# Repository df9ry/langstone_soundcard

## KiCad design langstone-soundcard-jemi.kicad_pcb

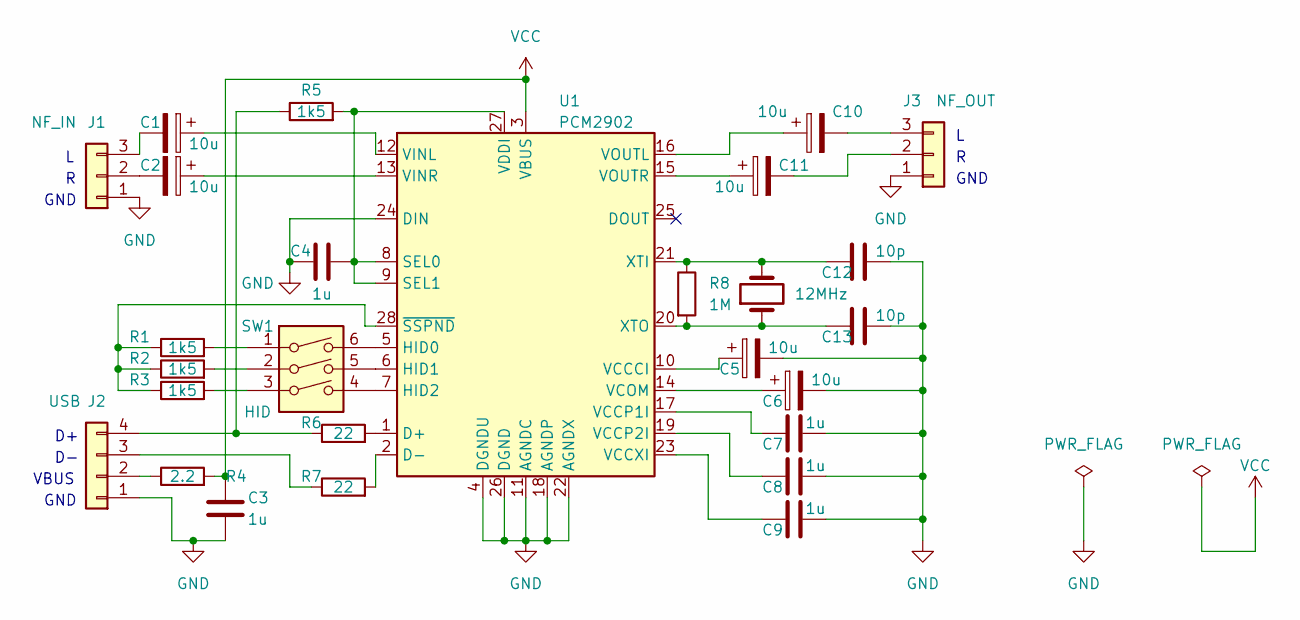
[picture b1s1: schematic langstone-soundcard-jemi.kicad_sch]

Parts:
C1, C2, C5, C6, C10, C11: 10u; CP_EIA-3216-18_Kemet-A_Pad1.58x1.35mm_HandSolder
C3, C4, C7, C8, C9: 1u; C_0603_1608Metric_Pad1.08x0.95mm_HandSolder
C12, C13: 10p; C_0603_1608Metric_Pad1.08x0.95mm_HandSolder
J1: NF_IN; JST_PH_B3B-PH-K_1x03_P2.00mm_Vertical
J2: USB; JST_PH_B4B-PH-K_1x04_P2.00mm_Vertical
J3: NF_OUT; JST_PH_B3B-PH-K_1x03_P2.00mm_Vertical
R1, R2, R3, R5: 1k5; R_0603_1608Metric_Pad0.98x0.95mm_HandSolder
R4: 2.2; R_0603_1608Metric_Pad0.98x0.95mm_HandSolder
R6, R7: 22; R_0603_1608Metric_Pad0.98x0.95mm_HandSolder
R8: 1M; R_0603_1608Metric_Pad0.98x0.95mm_HandSolder
SW1: HID; SW_DIP_SPSTx03_Slide_KingTek_DSHP03TJ_W5.25mm_P1.27mm_JPin
U1: PCM2902; SSOP-28_5.3x10.2mm_P0.65mm
Y1: 12MHz; Crystal_SMD_G8-2Pin_3.2x1.5mm_HandSoldering

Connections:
GND: C3.2, C4.1, C5.2, C6.2, C7.2, C8.2, C9.2, C12.2, C13.2, J1.1, J2.1, J3.1, U1.4 (DGNDU), U1.11 (AGNDC), U1.18 (AGNDP), U1.22 (AGNDX), U1.24 (DIN), U1.26 (DGND)
unnamed: C1.1, U1.12 (VINL)
unnamed: C1.2, J1.3
unnamed: C2.1, U1.13 (VINR)
unnamed: C2.2, J1.2
unnamed: C4.2, R5.2, U1.8 (SEL0), U1.9 (SEL1), U1.27 (VDDI)
unnamed: C5.1, U1.10 (VCCCI)
unnamed: C6.1, U1.14 (VCOM)
unnamed: C7.1, U1.17 (VCCP1I)
unnamed: C8.1, U1.19 (VCCP2I)
unnamed: C9.1, U1.23 (VCCXI)
unnamed: C10.1, U1.16 (VOUTL)
unnamed: C10.2, J3.3
unnamed: C11.1, U1.15 (VOUTR)
unnamed: C11.2, J3.2
unnamed: C12.1, R8.1, U1.21 (XTI), Y1.2
unnamed: C13.1, R8.2, U1.20 (XTO), Y1.1
unnamed: J2.2, R4.1
unnamed: J2.3, R7.1
unnamed: J2.4, R5.1, R6.1
unnamed: R1.1, R2.1, R3.1, U1.28 (~SSPND)
unnamed: R1.2, SW1.1
unnamed: R2.2, SW1.2
unnamed: R3.2, SW1.3
unnamed: R6.2, U1.1 (D+)
unnamed: R7.2, U1.2 (D-)
unnamed: SW1.4, U1.7 (HID2)
unnamed: SW1.5, U1.6 (HID1)
unnamed: SW1.6, U1.5 (HID0)
VCC: C3.1, R4.2, U1.3 (VBUS)

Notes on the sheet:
GND
VBUS

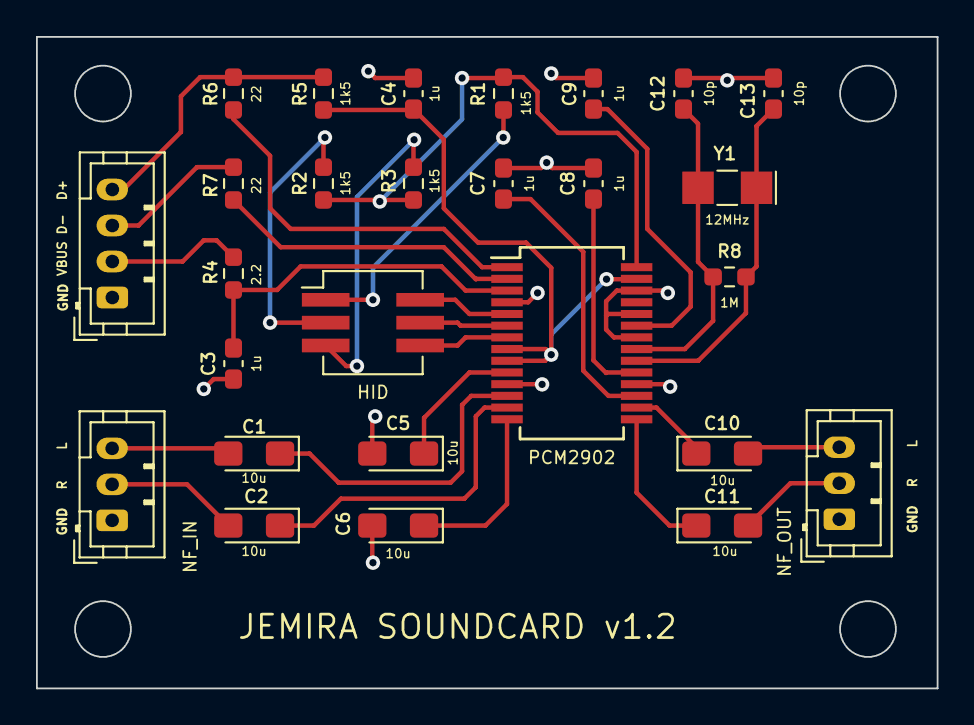
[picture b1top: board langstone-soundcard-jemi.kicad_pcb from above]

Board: 2 copper layers, 50.0 x 36.2 mm, 27 parts (0 on the bottom side), 30 nets.

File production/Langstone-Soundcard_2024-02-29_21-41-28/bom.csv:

Designator,Footprint,Quantity,Value,LCSC Part #
"C1, C10, C11, C2, C5, C6",CP_EIA-3216-18_Kemet-A_Pad1.58x1.35mm_HandSolder,6,10u,
"C12, C13",0805,2,10p,
"C3, C4, C7, C8, C9",0805,5,1u,
J1,JST_PH_B3B-PH-K_1x03_P2.00mm_Vertical,1,NF_IN,
J2,JST_PH_B4B-PH-K_1x04_P2.00mm_Vertical,1,USB,
J3,JST_PH_B3B-PH-K_1x03_P2.00mm_Vertical,1,NF_OUT,
"R1, R2, R3, R5",0805,4,1k5,
R4,0805,1,2.2,
"R6, R7",0805,2,22,
R8,0805,1,1M,
SW1,SW_DIP_SPSTx03_Slide_KingTek_DSHP03TJ_W5.25mm_P1.27mm_JPin,1,HID,
U1,SSOP-28_5.3x10.2mm_P0.65mm,1,PCM2902,
Y1,Crystal_SMD_G8-2Pin_3.2x1.5mm_HandSoldering,1,12MHz,

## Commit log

2024-01-28 Initial checkin
2024-01-29 Designregeln OK
2024-01-30 Production
2024-02-29 22pF auf 10pF geändert, Footprints auf SMD0805 geändert, SMD Quartz, SMD-Pin Regler auf SMD geändert. Stecker auf PH2.0 geändert.
2024-02-29 Jemi's Verkleinerung fertig
2024-02-29 schick gemacht
2024-03-27 v1.2
2024-03-27 v1.2.1
2024-03-27 Ready to submit to JLPCB
